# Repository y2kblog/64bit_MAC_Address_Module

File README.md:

# 64bit MACアドレスモジュール

## 概要

64bit MACアドレスモジュールはMicrochip社のI2C接続のMACアドレス書き込み済みEEPROM 24AA025E64を2.54mmピッチに変換したモジュールです。  
IPv6、ZigBee、FireWire等のネットワーク接続デバイスに一意の64bit MACアドレス(EUI-64)を割り当てることができます。  
ピンヘッダ含め部品は全て実装済みのため**はんだ付け作業は一切不要**です。また、**Arudinoシールド等に直接挿せるピン配置**となっているため、ジャンパワイヤ等を使わず手軽に接続できます。  
**MACアドレスを記載したカードを同梱。**

※48bit MACアドレス版は[こちら](https://github.com/y2kblog/48bit_MAC_Address_Module)

### 仕様
- 搭載IC：Microchip 24AA025E64T-I/OT
- メモリ容量：2Kbits (内ユーザ書込み可能領域：1Kbits)
- インターフェイス：I2C (最大400kHz)
- I2Cアドレス：0x50
- 電源電圧：1.7V～5.5V
- 最大消費電流
    - 読込み時：1mA
    - 書込み時：3mA
    - 待機時：1μA
- 基板サイズ：横10.0 mm × 縦7.5 mm

### 内容物
- 64bit MACアドレスモジュール本体
- MACアドレス記載カード

## 販売  
[スイッチサイエンス委託販売ページ](https://www.switch-science.com/catalog/5319/)  
※大量注文や在庫に関する問い合わせは[こちら](mailto:info.y2kb@gmail.com)までご連絡ください。  

### 回路図

### Arduinoによるプログラム例

#### 接続方法  

Arudino UNOの場合、下の写真のように挿すだけでOKです。

#### ミニマムコード

    #include <stdio.h>
    #include <stdint.h>
    #include <Wire.h>

    #define MAC_24AA02Exx_DEV_ADDR        0x50
    #define MAC_24AA02Exx_REG_ADDR_MAC    0xF8

    void setup() {
      Serial.begin(115200);
      while (!Serial);

      // execute ADC one time in order to power the Arduino AREF pin
      analogRead(A0);
      delay(1);  // Wait until the IC starts up

      // I2C init and read MAC address
      Wire.begin();
      Wire.setClock(100000);
      Wire.beginTransmission(MAC_24AA02Exx_DEV_ADDR);
      Wire.write(MAC_24AA02Exx_REG_ADDR_MAC);
      Wire.endTransmission(false);
      Wire.requestFrom(MAC_24AA02Exx_DEV_ADDR, 8);
      uint8_t MAC_addr_buf[8] = {'\0'};
      for(int i = 0; i < 8; i++)
        MAC_addr_buf[i] = Wire.read();

      // Determine whether the MAC address is EUI-48 or EUI-64
      int MAC_bytes;
      uint8_t MAC_addr[8] = {'\0'};
      if( (MAC_addr_buf[0] == 0xFF) && (MAC_addr_buf[1] == 0xFF) ) {
        MAC_bytes = 6;  // EUI-48 (24AA02xE48)
        memcpy(MAC_addr, MAC_addr_buf + 2, MAC_bytes);
      } else {
        MAC_bytes = 8;  // EUI-64 (24AA02xE64)
        memcpy(MAC_addr, MAC_addr_buf, MAC_bytes);
      }

      // print MAC address
      Serial.print(8 * MAC_bytes);
      Serial.print("bit MAC address : ");
      for(int i = 0; i < MAC_bytes; i++) {
        char strBuf[3];
        sprintf(strBuf, "%02X", MAC_addr[i]);
        Serial.print(strBuf);
        if(i < (MAC_bytes - 1))
          Serial.print("-");
      }
      Serial.println();
    }

    void loop() {
    }

### Nucleoによるプログラム例

#### 接続方法  

#### ソースコード

NUCLEO-L476RGのソースコードは[こちら](https://github.com/y2kblog/64bit_MAC_Address_Module/blob/master/SampleCode/NUCLEO-L476RG/24AA025Exx_testing) (IDE：SW4STM32)

## License
MIT License, see LICENSE.txt.

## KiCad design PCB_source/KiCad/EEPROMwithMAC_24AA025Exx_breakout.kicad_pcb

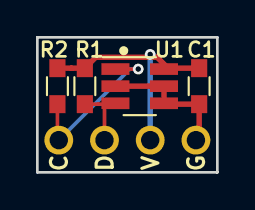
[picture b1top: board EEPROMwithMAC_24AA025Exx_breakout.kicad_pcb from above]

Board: 2 copper layers, 10.0 x 7.5 mm, 5 parts (1 on the bottom side), 4 nets.

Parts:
C1: 0.1u; USER_0603_HandSoldering
P1: CONN_01X04; USER_SIL-4_PinHeader2
R1, R2: 10k; USER_0603_HandSoldering
U1: 24AA02ExxT-I/OT; SOT-23-6_Handsoldering

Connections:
/SCL: P1.1, R2.2, U1.1
/SDA: P1.2, R1.2, U1.3
GND: C1.2, P1.4, U1.2, U1.4, U1.5
VCC: C1.1, P1.3, R1.1, R2.1, U1.6

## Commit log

2018-12-09 :neckbeard: Added .gitattributes & .gitignore files
2018-12-09 init
2018-12-16 add Nucleo sample code
2018-12-23 Add SalesPageLink
